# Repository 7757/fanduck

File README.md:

<p align="center"><strong>简体中文</strong> · <a href="README.en.md">English</a></p>

# 超能花钱鸭 Fanduck · Microduck 已复刻成功

> **基于官方项目完成复刻**：本项目基于 Pollen Robotics 官方公开的 [Microduck 代码](https://github.com/pollen-robotics/microduck) 与 [模型资料](https://github.com/pollen-robotics/microduck_rl) 制作。感谢官方团队的分享！

**[官方项目](https://github.com/pollen-robotics/microduck) · [官方官网](https://pollen-robotics.com/microduck/) · [我们的官网](https://duck.fandcode.com/)**

**我们的 Microduck 已经复刻成功！** 从零件采购、3D 打印到装配与调试，我们完成了从 0 到 1 的实机复刻，下面的照片和视频就是这只鸭子的实拍。

Fanduck 是对 Pollen Robotics Microduck 的非官方个人研究复刻。这里分享本次复刻所用的制作资料：物料清单、打印文件、板件资料、制作工具，以及查看鸭子 3D 姿态的镜像工作台。资料与项目官网同步存放，方便大家参考和交流。

## 我们的鸭子

## 实机演示

**实拍一**

**实拍二**

## 在线文档

[在线配件清单（腾讯文档）](https://docs.qq.com/sheet/DT0hMTFJIUktwa1hM?no_promotion=1&is_blank_or_template=blank&tab=BB08J2)：全部配件与采购链接，与官网入口一致。

## 制作资料下载

当前资料版本：`maker-20260916`。以下 4 个 ZIP 与官网发布目录中的文件完全一致。

| 资料包 | 包含什么 | 下载 |
| --- | --- | --- |
| 制作物料与打印文件 | 物料清单、中文分类打印件、装配图 | [ZIP · 12.7 MB](downloads/maker-20260916/fanduck-materials-print-20260916.zip?raw=true) |
| 板件制造资料 | Robot HAT、电池触点板、NFC 图纸及制造文件 | [ZIP · 31.3 MB](downloads/maker-20260916/fanduck-boards-20260916.zip?raw=true) |
| 制作工具源码 | 打印修正版生成、几何检查脚本及必要输入 | [ZIP · 1.1 MB](downloads/maker-20260916/fanduck-making-tools-20260916.zip?raw=true) |
| 3D 镜像工作台源码 | 3D 姿态显示、只读关节采集、可选视频观察 | [ZIP · 2.6 MB](downloads/maker-20260916/fanduck-mirror-workbench-20260916.zip?raw=true) |

第一次看这个项目，可以先下载“制作物料与打印文件”，从包内的 `01_物料清单.md` 开始。其余包按需要下载，使用前阅读各自的 README。

下载清单见 [manifest.json](downloads/maker-20260916/manifest.json)，完整性校验见 [SHA256SUMS.txt](downloads/maker-20260916/SHA256SUMS.txt)。在 macOS 或安装了 `shasum` 的终端中，从仓库根目录运行：

```bash
cd downloads/maker-20260916
shasum -a 256 -c SHA256SUMS.txt
```

## DCHUB 设计图

DCHUB v1.1 四口长条分线板（43 × 13 mm），含 KiCad 源文件、PCB 图、Gerber、BOM 和 3D 预览。

[浏览图纸与说明](hardware/dchub-v1.1/) · [下载完整设计包](downloads/dchub-v1.1-20261030/fanduck-dchub-v1.1-design.zip?raw=true) · [原理图 PDF](downloads/dchub-v1.1-20261030/fanduck-dchub-v1.1-schematic.pdf) · [SHA-256](downloads/dchub-v1.1-20261030/SHA256SUMS.txt) · [官网下载](https://duck.fandcode.com/#downloads)

本项目衍生设计，非官方 1:1 板；无稳压与保护电路，实物负载及 IMU 接线待验证。使用边界见[设计说明](hardware/dchub-v1.1/README.md)。

## 来源与许可

感谢 [Pollen Robotics](https://github.com/pollen-robotics/microduck) 公开的 Microduck 资料。上游来源、版本、许可与署名保留在各个包内，见 `SOURCES.json`、`LICENSES/` 及 README。

机械模型及衍生件保留上游的 **CC BY-SA-NC 非商业许可**，软件许可不能覆盖模型的商业使用；本项目不代表完整开源硬件。具体范围见[许可与来源说明](LICENSES.md)，打印、板件和设备连接的使用限制请以包内说明为准。

欢迎 Star 收藏资料，也欢迎分享你的制作进展。项目更新、照片与视频继续发布在 **[超能花钱鸭官网](https://duck.fandcode.com/)**。

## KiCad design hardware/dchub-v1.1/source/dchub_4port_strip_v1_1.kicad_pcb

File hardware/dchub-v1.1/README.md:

# DCHUB 四口长条分线板 v1.1

43 × 13 mm 的无源电源／信号分线板：4 个并联 X3P 三针座、独立两针电池入口及 470 µF / 16 V 电容。本项目重新绘制，**不是 Pollen Robotics 官方 1:1 板**。

[原理图 PDF](review/Schematic.pdf) · [PCB 顶面](review/PCB_top.svg) · [PCB 底面（镜像）](review/PCB_bottom_mirrored.svg) · [3D 预览](review/3D_top_iso.png)

## 下载与编辑

- `source/dchub_4port_strip_v1_1.kicad_pro`：KiCad 工程，含原理图、PCB、本地符号和封装库。
- `manufacturing/JLCPCB_UPLOAD_DCHUB_4P_LONG_v1.1.zip`：原始 Gerber／钻孔包；`gerbers/` 为逐层文件。
- `manufacturing/pcba/`：BOM、坐标与插件方向说明；装配 BOM 电容为 Rubycon `16ZLH470MEFC8X11.5`，3.5 mm 脚距。`source/` 中的原设计 BOM 仅作历史追溯。
- `review/`：原理图、PCB、钻孔与 3D 图；保留的 ERC／DRC 报告为设计时检查结果，不代表实物验收。
- `SHA256SUMS.txt`：本目录文件校验值。

板规格：2 层 FR-4，1.6 mm 厚、2 oz 铜；无安装孔。四个 X3P 电气等价，1=GND、2=VBATT、3=DATA；J5.1=GND、J5.2=VBATT。更多来源和未验证项见 [provenance.json](source/provenance.json)。

## 使用边界

这是设计资料发布。实物电流、温升、连接器承载、机械配合和最新 IMU 接线仍待验证；本板没有稳压、保险丝、反接或过流保护，不能降低电池电压。XL330 公开电压范围为 3.7–6.0 V，满电 2S 电池约 8.4 V，不能据此直接接入。

首次检查须断开电池、舵机和 IMU，先核对通断与极性，再用 5.0 V、0.20 A 限流电源空载验证；持续限流、温升、异味或极性不符立即断电。整机负载与 IMU 针序确认前不连接真机。

## 来源与许可

- 本项目本地设计：`deliverables/Microduck_DCHUB_四口长条分线板_v1.1_20260929/`；原设计／来源核对日期 2026-09-29，公开整理日期 2026-10-30。设计源无上游 Git 提交号。
- [Pollen Robot HAT](https://github.com/pollen-robotics/elec_RPI_Robot_HAT/tree/23eab11927f95ceca0dfa35bf182caeb7db39ea0)，提交 `23eab11927f95ceca0dfa35bf182caeb7db39ea0`：官方连接器与电源针序参考，Apache-2.0 原文保存在 `LICENSES/`。
- [ROBOTIS e-Manual](https://emanual.robotis.com/docs/en/dxl/x/xc330-m288/) 与 [JST EH](https://www.jst-mfg.com/product/index.php?lang=2&series=58)：制造商针序、尺寸及额定值参考，核对日期见来源文件。
- 第三方 `DCHUB.epro2` 仅作并联拓扑参考，许可未知，未再分发；原文件 SHA-256 保留在来源文件中。

上游许可与署名继续适用。本次公开不为全部自制板件额外指定统一许可，不授予商业制造授权；软件的 Apache-2.0 不自动覆盖整块板的设计。

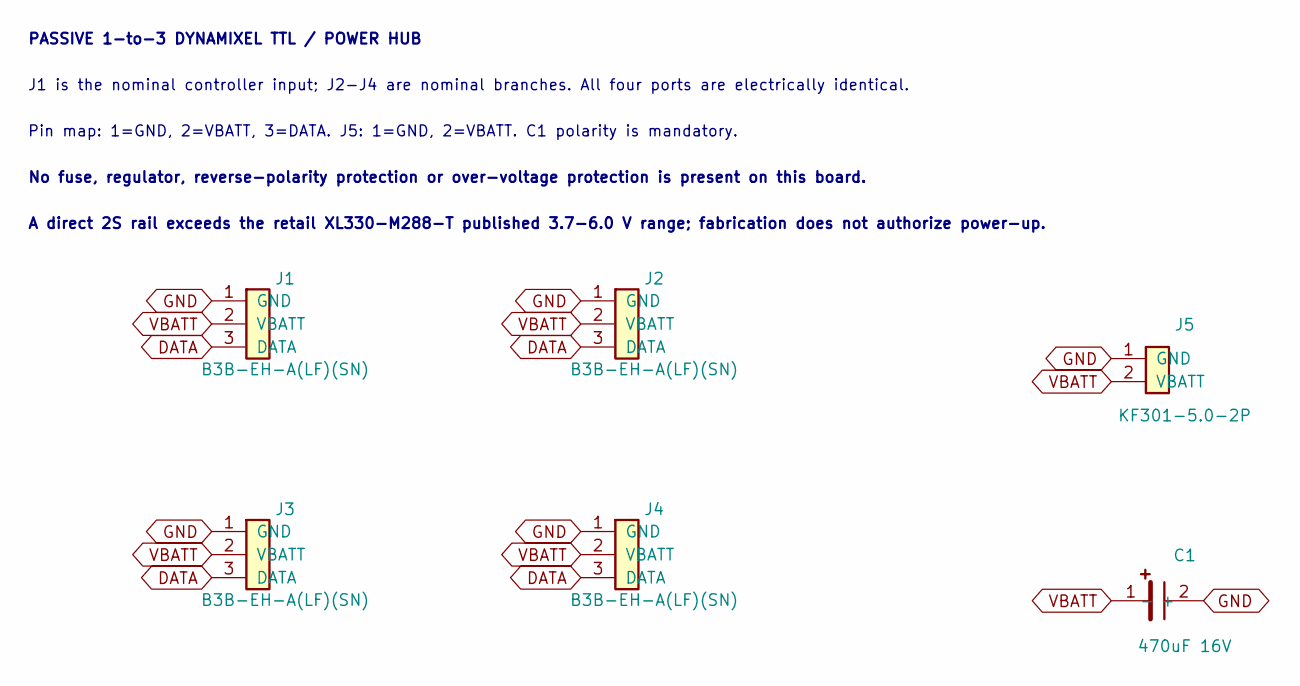
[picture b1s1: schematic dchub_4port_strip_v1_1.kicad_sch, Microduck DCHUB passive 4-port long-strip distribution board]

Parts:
C1: 470uF 16V; CP_Radial_D8.0mm_P3.50mm_Vertical
J1, J2, J3, J4: B3B-EH-A(LF)(SN); JST_EH_B3B-EH-A_1x03_P2.50mm_Vertical_Rot90
J5: KF301-5.0-2P

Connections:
DATA: J1.3 (DATA), J2.3 (DATA), J3.3 (DATA), J4.3 (DATA)
GND: C1.2 (-), J1.1 (GND), J2.1 (GND), J3.1 (GND), J4.1 (GND), J5.1 (GND)
VBATT: C1.1 (+), J1.2 (VBATT), J2.2 (VBATT), J3.2 (VBATT), J4.2 (VBATT), J5.2 (VBATT)

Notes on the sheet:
PASSIVE 1-to-3 DYNAMIXEL TTL / POWER HUB
J1 is the nominal controller input; J2-J4 are nominal branches. All four ports are electrically identical.
Pin map: 1=GND, 2=VBATT, 3=DATA. J5: 1=GND, 2=VBATT. C1 polarity is mandatory.
No fuse, regulator, reverse-polarity protection or over-voltage protection is present on this board.
A direct 2S rail exceeds the retail XL330-M288-T published 3.7-6.0 V range; fabrication does not authorize power-up.

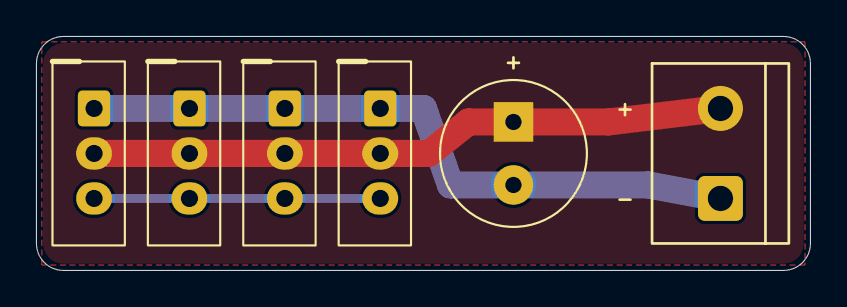
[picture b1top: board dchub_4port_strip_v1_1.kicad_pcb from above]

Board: 2 copper layers, 43.0 x 13.0 mm, 6 parts (0 on the bottom side), 3 nets.

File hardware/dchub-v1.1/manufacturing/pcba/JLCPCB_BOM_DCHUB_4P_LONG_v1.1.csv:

Comment,Designator,Footprint,LCSC Part #,Manufacturer,Manufacturer Part Number,Quantity per PCB,Assembly Type
"B3B-EH-A(LF)(SN)","J1,J2,J3,J4","DCHUB:JST_EH_B3B-EH-A_1x03_P2.50mm_Vertical_Rot90","C160259","JST","B3B-EH-A(LF)(SN)",4,"THT"
"KF301-5.0-2P","J5","DCHUB:KF301-5.0-2P","C474881","KEFA","KF301-5.0-2P",1,"THT"
"470uF 16V","C1","DCHUB:CP_Radial_D8.0mm_P3.50mm_Vertical","C109066","Rubycon","16ZLH470MEFC8X11.5",1,"THT polarized"
